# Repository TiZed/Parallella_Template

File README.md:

Parallella_Template
===================

KiCad template for the Parallella board

This template includes a schematic hierarchical block with the four 
PEC connectors and the associate signals with each connector. The Samtec BTH 
connectors foot prints are included and placed aligned to the Parallella board. 
The board edges are marked as a comment for convenience.

Copy all files, or clone the repository, to the KiCad /template directory. 
Directory name should be 'Parallella_Template'.

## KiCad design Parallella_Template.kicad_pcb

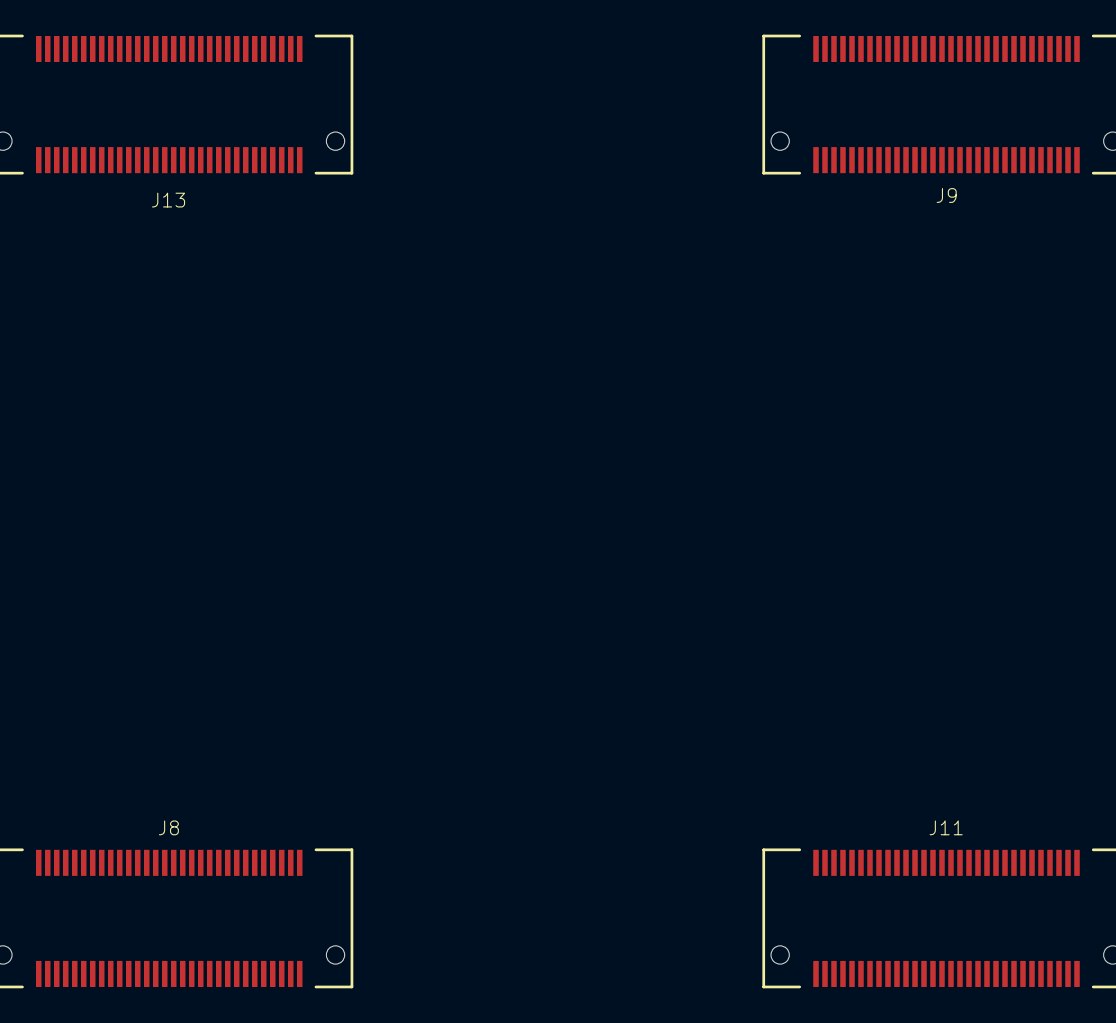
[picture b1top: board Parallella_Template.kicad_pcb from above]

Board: 2 copper layers, 4 parts (0 on the bottom side), 10 nets, no tracks yet.

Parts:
J8, J9, J11, J13: BTH-030-XX-X-D; BTH-030-XX-X-D-A

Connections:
1P0V: J13.43, J13.44
1P8V: J8.1, J8.2, J9.1, J9.2, J13.49, J13.50
1P35V: J13.48, J13.53
2P5V: J13.57, J13.58
3P3V: J13.59, J13.60
GND: J8.11, J8.12, J8.21, J8.22, J8.31, J8.32, J8.41, J8.42, J8.51, J8.52, J9.11, J9.12, J9.21, J9.22, J9.31, J9.32, J9.41, J9.42, J9.51, J9.52, J11.11, J11.12, J11.21, J11.22, J11.31, J11.32, J11.41, J11.42, J11.51, J11.52, J13.11, J13.12, J13.21, J13.22, J13.31, J13.32, J13.35, J13.36, J13.41, J13.42, J13.51, J13.52
SYS_5P0V: J13.1, J13.2
VDD_ADJ: J13.47, J13.54
VDD_DSP: J13.45, J13.46
VDD_GPIO: J11.1, J11.2, J13.55, J13.56

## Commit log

2014-05-09 First commit. Schematic done with all signals.
2014-05-09 Start of layout
2014-05-11 Created hierarchy in schematic. Final connectors layout.
2014-05-11 Added meta directory with icon and description.
2014-05-12 Fixed bad template title and edited the discription. jpg icon changed to png.
2014-05-12 Put some content in the README.
2014-06-02 Fixed bad library reference. Now pointing to the Samtec lib on Github and added the samtec.lib file.
